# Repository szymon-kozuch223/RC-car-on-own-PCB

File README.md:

# RC Car — Self-Designed PCB, 3D-Printed
RWD RC car built around my own custom PCB designed in KiCad, including a self-designed step-down converter (LM2596T-based), plus a custom controller, with chassis and remote fully 3D-printed. Communication via nRF24L01, Arduino Nano, 3S Li-ion 18650 power supply.

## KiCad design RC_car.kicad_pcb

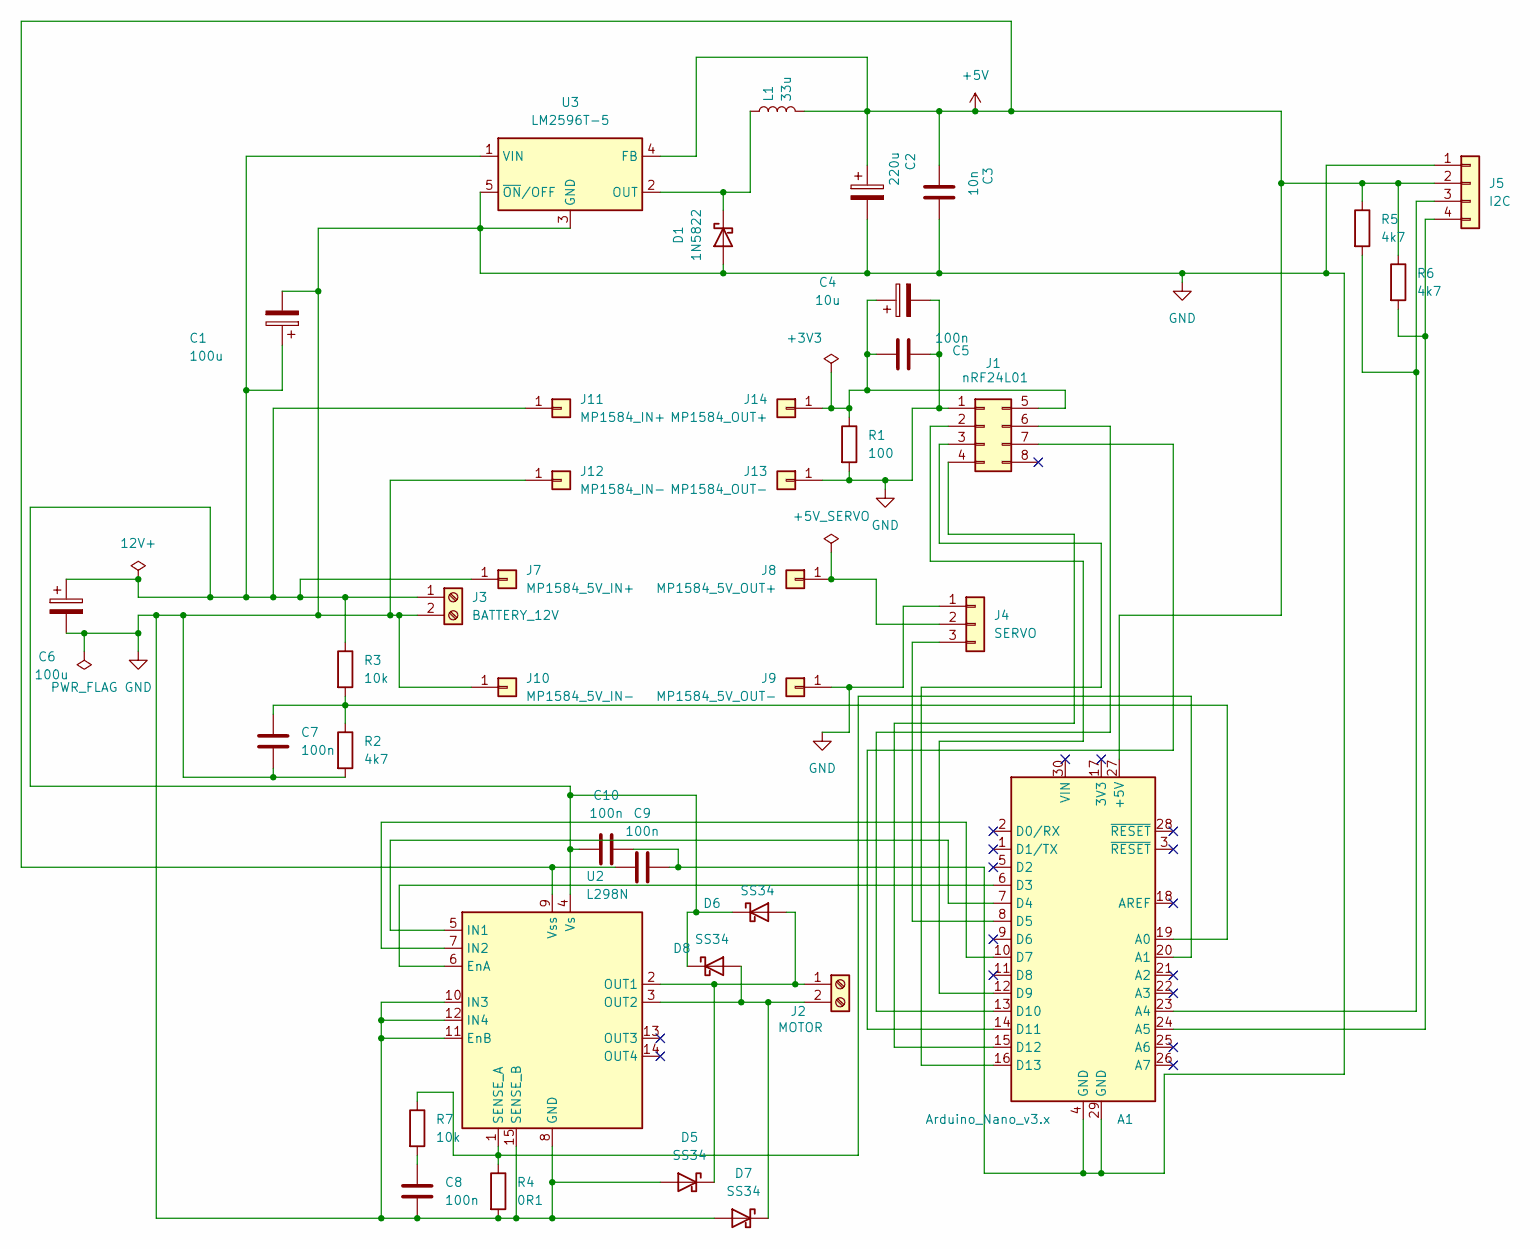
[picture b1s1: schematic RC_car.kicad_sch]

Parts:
A1: Arduino_Nano_v3.x; Arduino_Nano
C1, C6: 100u; CP_Radial_D8.0mm_P3.50mm
C2: 220u; CP_Radial_D8.0mm_P3.50mm
C3: 10n; C_Disc_D5.0mm_W2.5mm_P5.00mm
C4: 10u; CP_Radial_D8.0mm_P3.50mm
C5, C7, C8, C9, C10: 100n; C_Disc_D5.0mm_W2.5mm_P5.00mm
D1: 1N5822; D_DO-201AD_P15.24mm_Horizontal
D5, D6, D7, D8: SS34; D_DO-201AD_P15.24mm_Horizontal
J1: nRF24L01; PinSocket_2x04_P2.54mm_Vertical
J2: MOTOR; TerminalBlock_RND_205-00001_1x02_P5.00mm_Horizontal
J3: BATTERY_12V; TerminalBlock_RND_205-00001_1x02_P5.00mm_Horizontal
J4: SERVO; PinHeader_1x03_P2.54mm_Vertical
J5: I2C; PinHeader_1x04_P2.54mm_Vertical
J7: MP1584_5V_IN+; TestPoint_THTPad_2.5x2.5mm_Drill1.2mm
J8: MP1584_5V_OUT+; TestPoint_THTPad_2.5x2.5mm_Drill1.2mm
J9: MP1584_5V_OUT-; TestPoint_THTPad_2.5x2.5mm_Drill1.2mm
J10: MP1584_5V_IN-; TestPoint_THTPad_2.5x2.5mm_Drill1.2mm
J11: MP1584_IN+; TestPoint_THTPad_2.5x2.5mm_Drill1.2mm
J12: MP1584_IN-; TestPoint_THTPad_2.5x2.5mm_Drill1.2mm
J13: MP1584_OUT-; TestPoint_THTPad_2.5x2.5mm_Drill1.2mm
J14: MP1584_OUT+; TestPoint_THTPad_2.5x2.5mm_Drill1.2mm
L1: 33u; L_Radial_D8.7mm_P5.00mm_Fastron_07HCP
R1: 100; R_Axial_DIN0207_L6.3mm_D2.5mm_P10.16mm_Horizontal
R2, R5, R6: 4k7; R_Axial_DIN0207_L6.3mm_D2.5mm_P10.16mm_Horizontal
R3, R7: 10k; R_Axial_DIN0207_L6.3mm_D2.5mm_P10.16mm_Horizontal
R4: 0R1; R_Axial_DIN0207_L6.3mm_D2.5mm_P10.16mm_Horizontal
U2: L298N; TO-220-15_P2.54x5.08mm_StaggerOdd_Lead4.58mm_Vertical
U3: LM2596T-5; TO-220-5_P3.4x3.7mm_StaggerEven_Lead3.8mm_Vertical

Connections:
+5V: A1.27 (+5V), C2.1, C3.1, C9.1, J5.2, L1.2, R5.1, R6.1, U2.9 (Vss), U3.4 (FB)
GND: A1.4 (GND), A1.29 (GND), C1.2, C2.2, C3.2, C4.2, C5.1, C6.2, C7.2, C8.2, C9.2, C10.2, D1.2 (A), D5.2 (A), D7.2 (A), J1.1 (Pin_a1), J3.2, J4.1, J5.1, J9.1 (Pin_1_1), J10.1 (Pin_1_1), J12.1 (Pin_1_1), J13.1 (Pin_1_1), R1.2, R2.2, R4.2, U2.8 (GND), U2.10 (IN3), U2.11 (EnB), U2.12 (IN4), U2.15 (SENSE_B), U3.3 (GND), U3.5 (~ON/OFF)
unnamed: A1.19 (A0), C7.1, R2.1, R3.2
unnamed: A1.20 (A1), R4.1, R7.1, U2.1 (SENSE_A)
unnamed: A1.23 (A4), J5.3, R5.2
unnamed: A1.24 (A5), J5.4, R6.2
unnamed: A1.6 (D3), U2.6 (EnA)
unnamed: A1.7 (D4), U2.5 (IN1)
unnamed: A1.8 (D5), J4.3
unnamed: A1.10 (D7), U2.7 (IN2)
unnamed: A1.12 (D9), J1.2 (Pin_a2)
unnamed: A1.13 (D10), J1.6 (Pin_b2)
unnamed: A1.14 (D11), J1.7 (Pin_b3)
unnamed: A1.15 (D12), J1.4 (Pin_a4)
unnamed: A1.16 (D13), J1.3 (Pin_a3)
unnamed: C8.1, R7.2
unnamed: D1.1 (K), L1.1, U3.2 (OUT)
unnamed: D5.1 (K), D6.2 (A), J2.1, U2.2 (OUT1)
unnamed: C1.1, C6.1, C10.1, D6.1 (K), D8.1 (K), J3.1, J7.1 (Pin_1_1), J11.1 (Pin_1_1), R3.1, U2.4 (Vs), U3.1 (VIN)
unnamed: D7.1 (K), D8.2 (A), J2.2, U2.3 (OUT2)
unnamed: C4.1, C5.2, J1.5 (Pin_b1), J14.1 (Pin_1_1), R1.1
unnamed: J4.2, J8.1 (Pin_1_1)

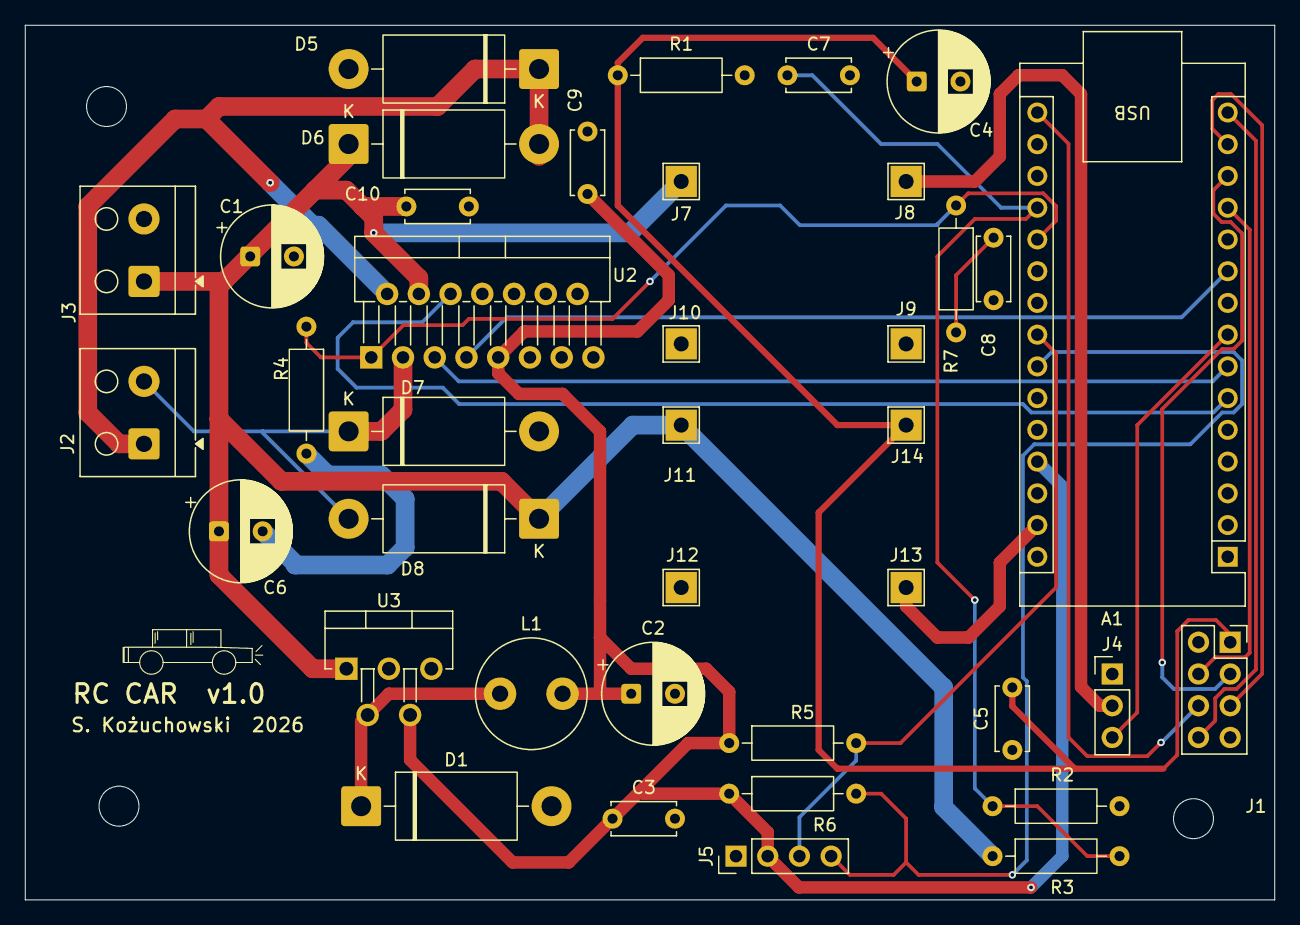
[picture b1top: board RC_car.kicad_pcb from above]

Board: 2 copper layers, 100.0 x 70.0 mm, 39 parts (0 on the bottom side), 22 nets.
